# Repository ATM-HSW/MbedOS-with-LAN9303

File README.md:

# LAN9303 shield for NUCLEO-144 and Mbed OS

## Introduction

## Hardware modification

The onboard Phy must be disabled. For this purpose, several solder bridges (0Ohm resistors) must be removed:
- from top: SB13
- from button: SB160, SB164, SB178, SB181, SB182, SB183

Snippets from the user manual UM1974 show the positions on top and bottom layer.

## Mbed OS integration

comming soon

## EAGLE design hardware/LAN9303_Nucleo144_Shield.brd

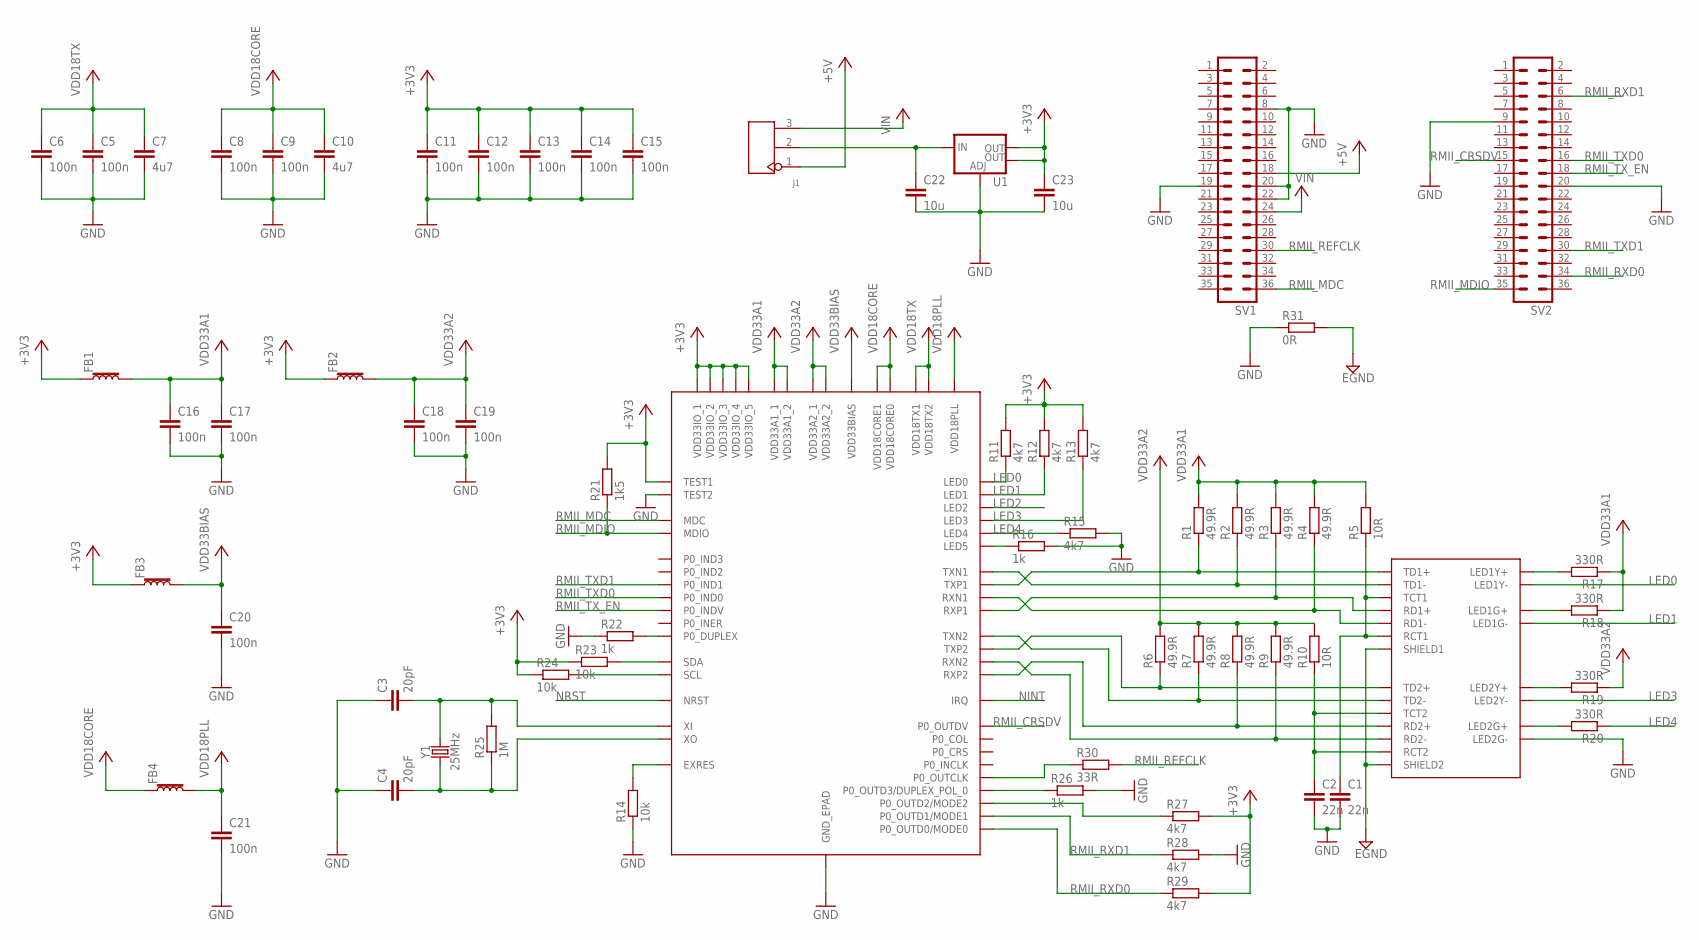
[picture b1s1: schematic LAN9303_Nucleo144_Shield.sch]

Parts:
C1, C2: 22n; C0603
C3, C4: 20pF; C0603
C5, C6, C8, C9, C11, C12, C13, C14, C15, C16, C17, C18, C19, C20, C21: 100n; C0603
C7, C10: 4u7; C0603
C22, C23: 10u; C1206
FB1, FB2, FB3, FB4: FERRITE_BEAD-0603; 0603
J1: DIP-BLACK-FEMALE-HEADER-VERT(3P-2.54); H3-2.54
R1, R2, R3, R4, R6, R7, R8, R9: 49.9R; R0603
R5, R10: 10R; R0603
R11, R12, R13, R15, R27, R28, R29: 4k7; R0603
R14, R23, R24: 10k; R0603
R16, R22, R26: 1k; R0603
R17, R18, R19, R20: 330R; R0603
R21: 1k5; R0603
R25: 1M; R0603
R30: 33R; R0603
R31: 0R; R0805
SV1, SV2: MA18-2
U1: V_REG_LM1117SOT223; SOT223
U$1: LAN9303; QFN56
U$2: WE_DUAL_RJ45JACK; DUAL_RJ45
Y1: 25MHz; CRYSTAL-SMD-5X3.2-2PAD

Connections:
+3V3: C11.1, C12.1, C13.1, C14.1, C15.1, C23.1, FB1.1, FB2.1, FB3.1, R11.2, R12.2, R13.2, R21.2, R23.1, R24.1, R27.2, R29.2, U1.2 (OUT), U1.4 (OUT), U$1.9 (VDD33IO_1), U$1.15 (VDD33IO_2), U$1.23 (VDD33IO_3), U$1.30 (VDD33IO_4), U$1.32 (VDD33IO_5), U$1.33 (TEST1)
+5V: J1.1, SV1.18
CLK_IN: R30.1, U$1.17 (P0_OUTCLK)
GND: C1.2, C2.2, C3.1, C4.1, C5.2, C6.2, C7.2, C8.2, C9.2, C10.2, C11.2, C12.2, C13.2, C14.2, C15.2, C16.2, C17.2, C18.2, C19.2, C20.2, C21.2, C22.2, C23.2, R14.1, R15.2, R16.2, R22.1, R26.2, R28.2, R31.1, SV1.8, SV1.19, SV1.20, SV1.22, SV2.9, SV2.20, U1.1 (ADJ), U$1.34 (TEST2), U$1.EPAD (GND_EPAD), U$2.P$2_12 (LED2G-)
GND1: R31.2, U$2.P$1_8 (SHIELD1), U$2.P$2_8 (SHIELD2)
LED0: R11.1, U$1.29 (LED0), U$2.P$1_10 (LED1Y-)
LED1: R12.1, U$1.28 (LED1), U$2.P$1_12 (LED1G-)
LED2: U$1.27 (LED2)
LED3: R13.1, U$1.26 (LED3), U$2.P$2_10 (LED2Y-)
LED4: R15.1, R20.1, U$1.25 (LED4)
unnamed: C2.1, R10.1, U$2.P$2_4 (TCT2), U$2.P$2_5 (RCT2)
unnamed: C1.1, R5.1, U$2.P$1_4 (TCT1), U$2.P$1_5 (RCT1)
unnamed: R22.2, U$1.20 (P0_DUPLEX)
unnamed: R16.1, U$1.24 (LED5)
unnamed: R17.2, U$2.P$1_9 (LED1Y+)
unnamed: R19.2, U$2.P$2_9 (LED2Y+)
unnamed: R20.2, U$2.P$2_11 (LED2G+)
unnamed: R18.2, U$2.P$1_11 (LED1G+)
unnamed: R23.2, U$1.35 (SDA)
unnamed: R24.2, U$1.36 (SCL)
unnamed: R14.2, U$1.49 (EXRES)
unnamed: R27.1, U$1.12 (P0_OUTD2/MODE2)
unnamed: C22.1, J1.2, U1.3 (IN)
unnamed: C3.2, R25.2, U$1.39 (XI), Y1.P$2 (2)
unnamed: C4.2, R25.1, U$1.40 (XO), Y1.P$1 (1)
unnamed: R26.1, U$1.11 (P0_OUTD3/DUPLEX_POL_0)
NINT: U$1.38 (IRQ)
NRST: U$1.37 (NRST)
RMII_CRSDV: SV2.15, U$1.16 (P0_OUTDV)
RMII_MDC: SV1.36, U$1.22 (MDC)
RMII_MDIO: R21.1, SV2.35, U$1.21 (MDIO)
RMII_REFCLK: R30.2, SV1.30
RMII_RXD0: R29.1, SV2.34, U$1.14 (P0_OUTD0/MODE0)
RMII_RXD1: R28.1, SV2.6, U$1.13 (P0_OUTD1/MODE1)
RMII_TXD0: SV2.16, U$1.5 (P0_IND0)
RMII_TXD1: SV2.30, U$1.4 (P0_IND1)
RMII_TX_EN: SV2.18, U$1.6 (P0_INDV)
RXN1: R4.1, U$1.45 (RXN1), U$2.P$1_6 (RD1-)
RXN2: R9.1, U$1.54 (RXN2), U$2.P$2_6 (RD2-)
RXP1: R3.1, U$1.46 (RXP1), U$2.P$1_3 (RD1+)
RXP2: R8.1, U$1.53 (RXP2), U$2.P$2_3 (RD2+)
TXN1: R2.1, U$1.42 (TXN1), U$2.P$1_2 (TD1-)
TXN2: R7.1, U$1.1 (TXN2), U$2.P$2_2 (TD2-)
TXP1: R1.1, U$1.43 (TXP1), U$2.P$1_1 (TD1+)
TXP2: R6.1, U$1.56 (TXP2), U$2.P$2_1 (TD2+)
VDD18CORE: C8.1, C9.1, C10.1, FB4.1, U$1.10 (VDD18CORE0), U$1.31 (VDD18CORE1)
VDD18PLL: C21.1, FB4.2, U$1.41 (VDD18PLL)
VDD18TX: C5.1, C6.1, C7.1, U$1.48 (VDD18TX1), U$1.51 (VDD18TX2)
VDD33A1: C16.1, C17.1, FB1.2, R1.2, R2.2, R3.2, R4.2, R5.2, R17.1, R18.1, U$1.44 (VDD33A1_1), U$1.47 (VDD33A1_2)
VDD33A2: C18.1, C19.1, FB2.2, R6.2, R7.2, R8.2, R9.2, R10.2, R19.1, U$1.52 (VDD33A2_1), U$1.55 (VDD33A2_2)
VDD33BIAS: C20.1, FB3.2, U$1.50 (VDD33BIAS)
VIN: J1.3, SV1.24

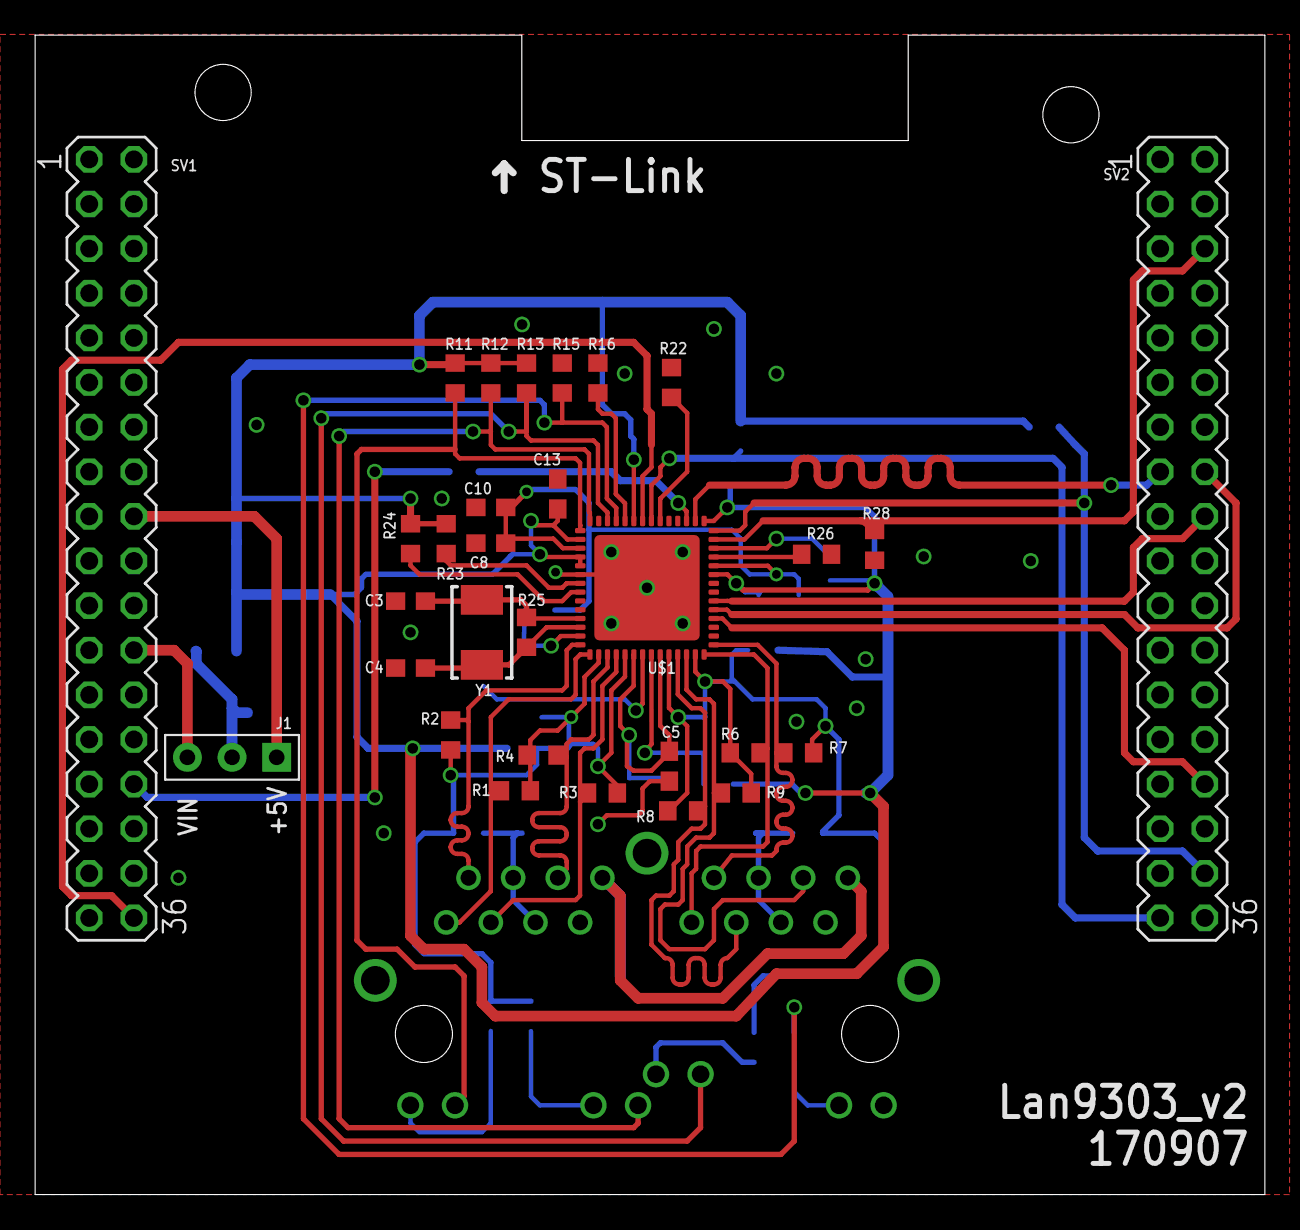
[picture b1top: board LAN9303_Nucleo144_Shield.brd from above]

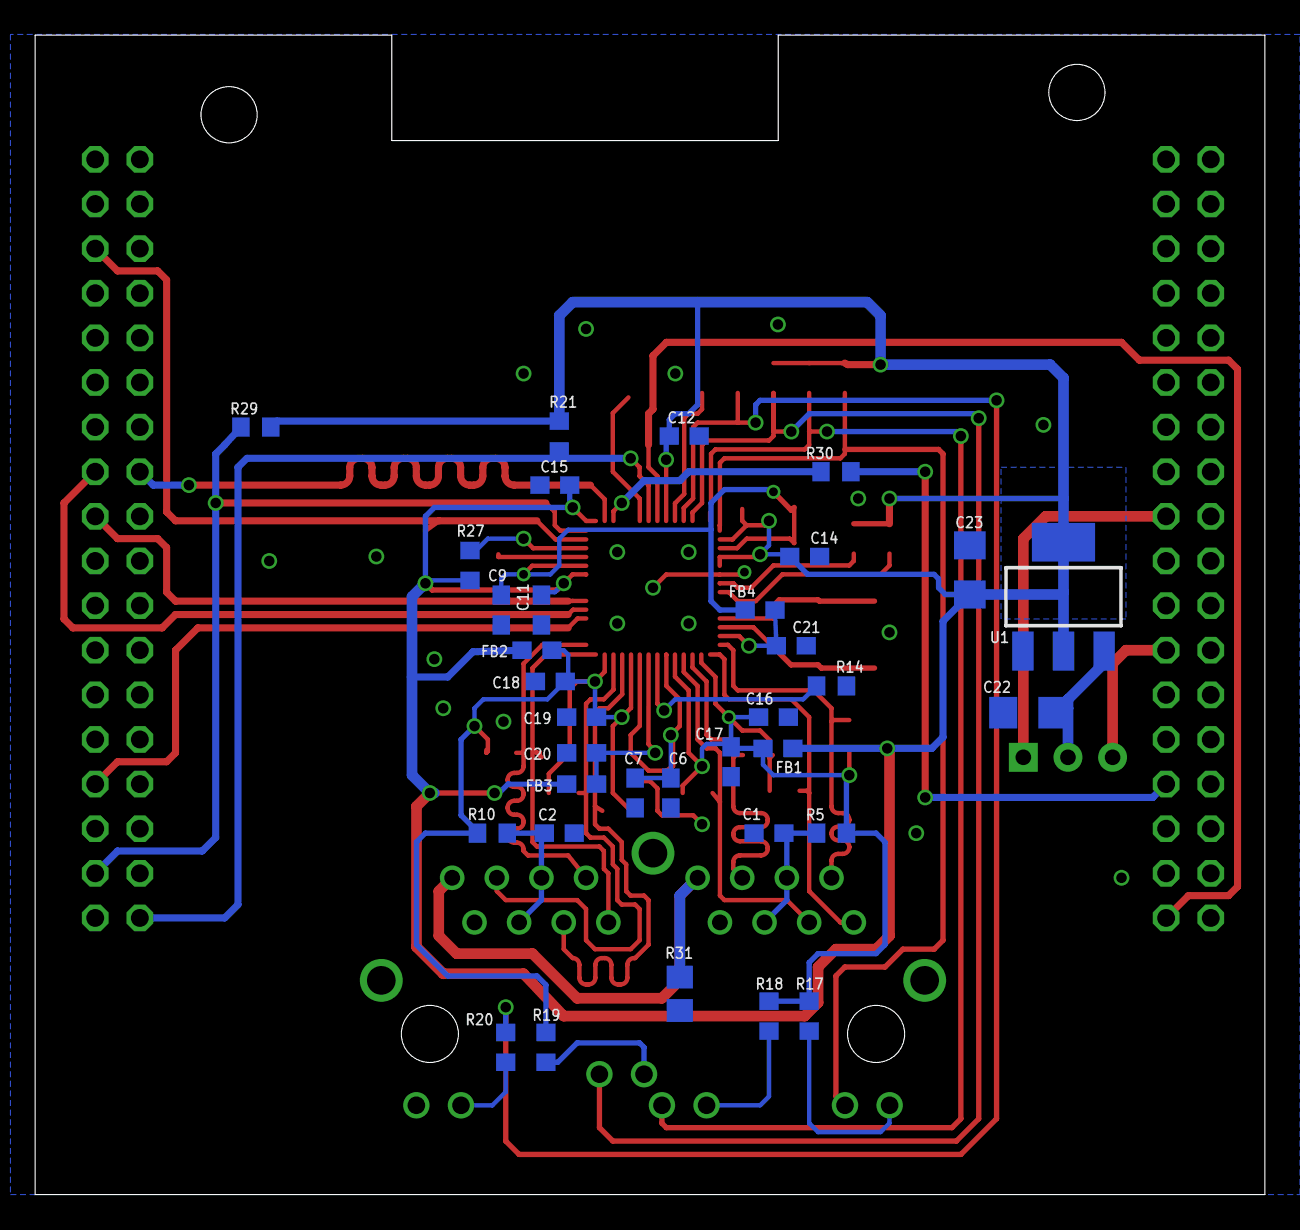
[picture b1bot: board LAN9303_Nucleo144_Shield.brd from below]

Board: 2 copper layers, 70.0 x 66.0 mm, 65 parts (34 on the bottom side), 49 nets.

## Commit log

2019-07-23 initial commit - not yet completed

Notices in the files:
parts and their libraries:
SparkFun-Coils: Licensing: Creative Commons ShareAlike 4.0 International - https://creativecommons.org/licenses/by-sa/4.0
